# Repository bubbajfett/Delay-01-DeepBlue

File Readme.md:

Delay pedal modeled after the deep blue delay.   Copyright belongs to owner.

First version was busted and fried the PT2399 chip due to incorrect footprints.

V2 works.

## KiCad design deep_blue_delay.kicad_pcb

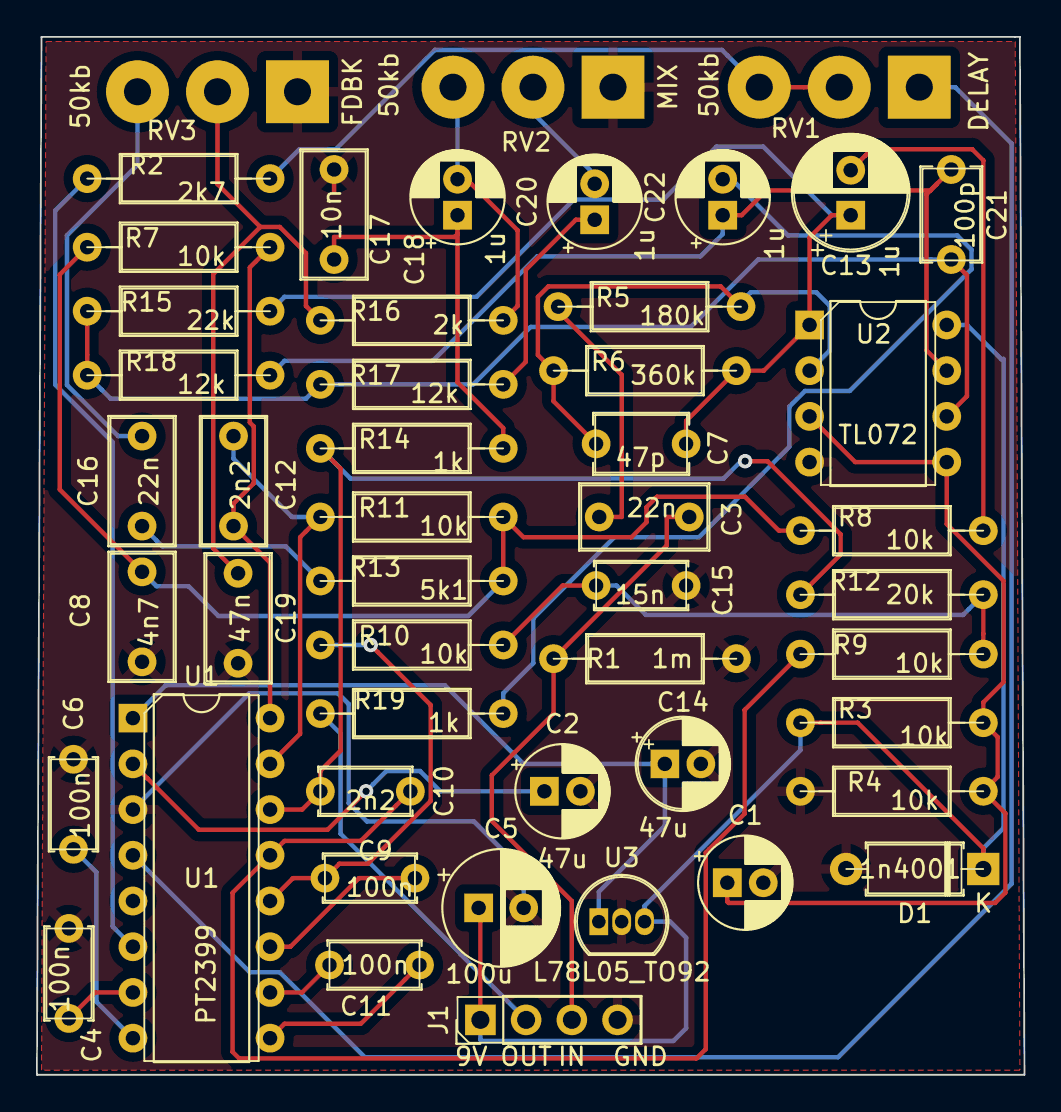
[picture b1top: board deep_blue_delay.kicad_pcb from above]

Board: 2 copper layers, 54.9 x 57.7 mm, 49 parts (0 on the bottom side), 36 nets.

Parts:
C1, C2, C14: 47u; CP_Radial_D5.0mm_P2.00mm
C3, C16: 22n; C_Rect_L7.0mm_W3.5mm_P5.00mm
C4, C6, C9, C11: 100n; C_Disc_D5.0mm_W2.5mm_P5.00mm
C5: 100u; CP_Radial_D6.3mm_P2.50mm
C7: 47p; C_Disc_D5.1mm_W3.2mm_P5.00mm
C8: 4n7; C_Rect_L7.0mm_W3.5mm_P5.00mm
C10: 2n2; C_Disc_D5.0mm_W2.5mm_P5.00mm
C12: 2n2; C_Rect_L7.0mm_W3.5mm_P5.00mm
C13: 1u; CP_Radial_D6.3mm_P2.50mm
C15: 15n; C_Disc_D5.0mm_W2.5mm_P5.00mm
C17: 10n; C_Rect_L7.0mm_W3.5mm_P5.00mm
C18, C20, C22: 1u; CP_Radial_D5.0mm_P2.00mm
C19: 47n; C_Rect_L7.0mm_W3.5mm_P5.00mm
C21: 100p; C_Disc_D5.1mm_W3.2mm_P5.00mm
D1: 1n4001; D_A-405_P7.62mm_Horizontal
J1: Conn_01x05; PinHeader_1x04_P2.54mm_Vertical
R1: 1m; R_Axial_DIN0207_L6.3mm_D2.5mm_P10.16mm_Horizontal
R2: 2k7; R_Axial_DIN0207_L6.3mm_D2.5mm_P10.16mm_Horizontal
R3, R4, R7, R8, R9, R10, R11: 10k; R_Axial_DIN0207_L6.3mm_D2.5mm_P10.16mm_Horizontal
R5: 180k; R_Axial_DIN0207_L6.3mm_D2.5mm_P10.16mm_Horizontal
R6: 360k; R_Axial_DIN0207_L6.3mm_D2.5mm_P10.16mm_Horizontal
R12: 20k; R_Axial_DIN0207_L6.3mm_D2.5mm_P10.16mm_Horizontal
R13: 5k1; R_Axial_DIN0207_L6.3mm_D2.5mm_P10.16mm_Horizontal
R14, R19: 1k; R_Axial_DIN0207_L6.3mm_D2.5mm_P10.16mm_Horizontal
R15: 22k; R_Axial_DIN0207_L6.3mm_D2.5mm_P10.16mm_Horizontal
R16: 2k; R_Axial_DIN0207_L6.3mm_D2.5mm_P10.16mm_Horizontal
R17, R18: 12k; R_Axial_DIN0207_L6.3mm_D2.5mm_P10.16mm_Horizontal
RV1, RV2, RV3: 50kb; SolderWirePad_1x03_P4.445mm_Drill1.5mm
U1: PT2399; DIP-16_W7.62mm
U2: TL072; DIP-8_W7.62mm
U3: L78L05_TO92; TO-92_Inline

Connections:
+9V: C5.1, D1.1 (K), J1.1, R3.1, U2.8 (V+), U3.3 (VI)
GND: C1.2, C2.2, C4.1, C5.2, C6.1, C8.2, C14.2, C15.1, C17.1, C19.1, D1.2 (A), J1.4, R1.1, R4.2, RV2.1, RV3.1, U1.3 (AGND), U2.4 (V-), U3.2 (GND)
IN: C3.2, J1.3, R1.2
unnamed: C2.1, U1.2 (REF)
unnamed: C3.1, R5.2
unnamed: C4.2, U1.7 (CC1)
unnamed: C6.2, U1.8 (CC0)
unnamed: C7.2, R5.1, R6.2, U2.2 (-)
unnamed: C8.1, R7.2, R8.1, R11.2, R13.1
unnamed: C9.1, R10.1, U1.12 (OP2-OUT)
unnamed: C9.2, U1.11 (OP2-IN)
unnamed: C10.1, R12.2, R14.1, U1.14 (LPF2-OUT)
unnamed: C10.2, R9.1, U1.13 (LPF2-IN)
unnamed: C11.1, U1.10 (OP1-IN)
unnamed: C11.2, U1.9 (OP1-OUT)
unnamed: C12.1, R7.1, U1.16 (LPF1-IN)
unnamed: C12.2, R11.1, U1.15 (LPF1-OUT)
unnamed: C7.1, C13.1, R6.1, R15.1, U2.1
unnamed: C13.2, R8.2
unnamed: C15.2, R9.2, R10.2, R12.1
unnamed: C16.1, R13.2
unnamed: C16.2, RV3.3
unnamed: C17.2, C18.1, R14.2
unnamed: C18.2, R16.1, RV2.3
unnamed: C19.2, R16.2, RV3.2
unnamed: C20.1, R17.2
unnamed: C20.2, RV2.2
unnamed: C21.1, C22.1, R18.2, U2.7
unnamed: C21.2, R15.2, R17.1, R18.1, U2.6 (-)
unnamed: C22.2, R19.2
unnamed: R2.1, U1.6 (VCO)
unnamed: R2.2, RV1.2, RV1.3
unnamed: RV1.1, U1.4 (DGND)
OUT: J1.2, R19.1
VB: C1.1, R3.2, R4.1, U2.3 (+), U2.5 (+)
VD: C14.1, U1.1 (VCC), U3.1 (VO)

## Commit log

2026-01-28 re-plotted
2026-02-06 added license
